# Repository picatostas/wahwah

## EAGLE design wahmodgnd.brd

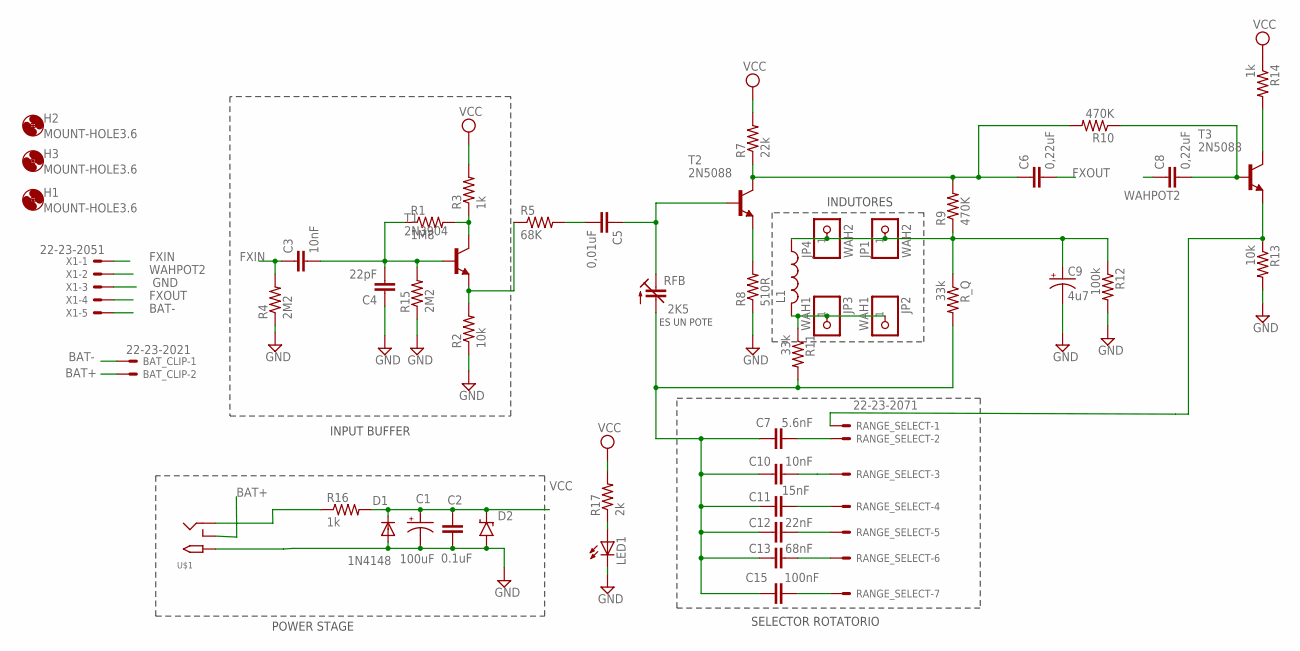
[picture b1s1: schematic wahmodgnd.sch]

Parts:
BAT_CLIP: 22-23-2021
C1: 100uF; E2,5-5
C2: 0.1uF; C025-025X050
C3: 10nF; C050-025X075
C4: 22pF; C050-025X075
C5: 0,01uF; C050-035X075
C6, C8: 0,22uF; C050-035X075
C7: 5.6nF; C050-030X075
C9: 4u7; E2,5-6
C10: 10nF; C050-030X075
C11: 15nF; C050-030X075
C12: 22nF; C050-030X075
C13: 68nF; C050-030X075
C15: 100nF; C050-030X075
D1: 1N4148; DO35-7
D2: 1N9ZENER; DO35-3
H1, H2, H3: MOUNT-HOLE3.6; 3,6
JP1, JP4: WAH2; 1X01
JP2, JP3: WAH1; 1X01
L1: WAH
LED1: TLLY4400; LED3MM
R1: 1M8; 0204/7
R2, R13: 10k; 0204/7
R3, R14, R16: 1k; 0204/7
R4, R15: 2M2; 0204/7
R5: 68K; 0204/7
R7: 22k; 0204/7
R8: 510R; 0204/7
R9, R10: 470K; 0204/7
R11: 33k; 0204/7
R12: 100k; 0204/7
R17: 2k; 0204/7
RANGE_SELECT: 22-23-2071
RFB: 2K5; CTRIM808-BC7.5
R_Q: 33k; 0204/7
T1: 2N3904; TO92
T2, T3: 2N5088; TO92
U$1: 2.1MMJACKTHM; PJ-102A
X1: 22-23-2051

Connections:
BAT+: BAT_CLIP.2, U$1.RING_SW
BAT-: BAT_CLIP.1, X1.5
FXIN: C3.1, R4.2, X1.1
FXOUT: C6.2, X1.4
GND: C1.-, C2.2, C4.1, C9.-, D1.A, D2.A, LED1.K (C), R2.1, R4.1, R8.1, R12.2, R13.2, R15.1, U$1.TIP, X1.3
unnamed: C3.2, C4.2, R1.1, R15.2, T1.2 (B)
unnamed: R2.2, R5.1, T1.3 (E)
unnamed: R16.1, U$1.RING
unnamed: JP2.1, JP3.1, L1.2, R11.1
unnamed: R1.2, R3.1, T1.1 (C)
unnamed: R13.1, RANGE_SELECT.1, T3.3 (E)
unnamed: C5.2, R5.2
unnamed: C5.1, RFB.1 (E), T2.2 (B)
unnamed: C6.1, R7.1, R9.2, R10.2, T2.1 (C)
unnamed: C7.2, RANGE_SELECT.2
unnamed: C10.2, RANGE_SELECT.3
unnamed: C9.+, JP1.1, JP4.1, L1.1, R9.1, R12.1, R_Q.1
unnamed: C11.2, RANGE_SELECT.4
unnamed: C12.2, RANGE_SELECT.5
unnamed: C7.1, C10.1, C11.1, C12.1, C13.1, C15.1, R11.2, RFB.2 (A), R_Q.2
unnamed: C13.2, RANGE_SELECT.6
unnamed: R8.2, T2.3 (E)
unnamed: R14.2, T3.1 (C)
unnamed: C15.2, RANGE_SELECT.7
unnamed: LED1.A, R17.1
unnamed: C8.2, R10.1, T3.2 (B)
VCC: C1.+, C2.1, D1.C, D2.C, R3.2, R7.2, R14.1, R16.2, R17.2
WAHPOT2: C8.1, X1.2

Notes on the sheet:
POWER STAGE
INPUT BUFFER
INDUTORES
ES UN POTE
SELECTOR ROTATORIO

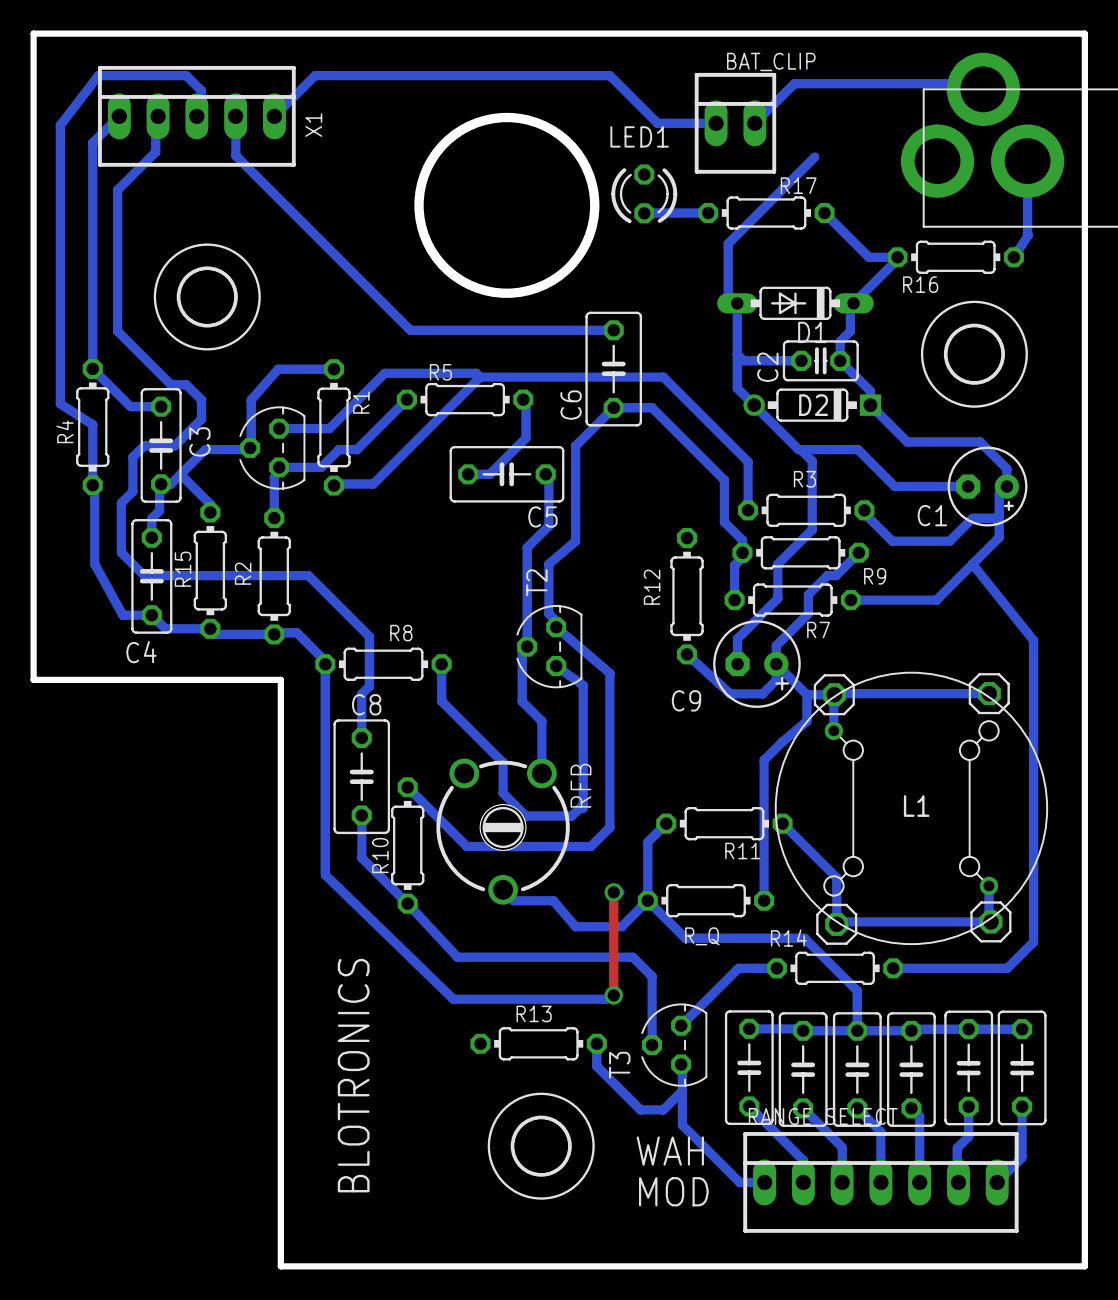
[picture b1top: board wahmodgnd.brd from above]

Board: 2 copper layers, 68.7 x 80.5 mm, 50 parts (0 on the bottom side), 28 nets.
